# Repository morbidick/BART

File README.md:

# BBQ Thermometer

## Hardware

### Board ([nrf52](https://www.adafruit.com/product/3406))

* [Arduino IDE Setup](https://learn.adafruit.com/bluefruit-nrf52-feather-learning-guide/arduino-bsp-setup)
* [pinout](https://learn.adafruit.com/bluefruit-nrf52-feather-learning-guide/device-pinout)
* [library](https://github.com/adafruit/Adafruit_nRF52_Arduino/)

### Probes

Some NTCs from Senstech (lets use pt1000 next time...) with a stero jack

### Bluetooth

* Environmental Sensing Service: [0x181A](https://www.bluetooth.com/specifications/gatt/viewer?attributeXmlFile=org.bluetooth.service.environmental_sensing.xml)
* Temperature Characteristic: [0x2A1F](https://www.bluetooth.com/specifications/gatt/viewer?attributeXmlFile=org.bluetooth.characteristic.temperature_celsius.xml)
* Payload 5 Bytes: First Byte `0x01` when probe is connected (`0x00` otherwise), int16 Temperature 1, int16 Temperature 2 (Celsius, Exponent -1)

## Frontend

Let's write an awesome PWA with web bluetooth

### Web Bluetooth API

* usage with chrome [activate](chrome://flags/#enable-experimental-web-platform-features) [debug](chrome://bluetooth-internals)
* [inspiration](https://www.youtube.com/watch?v=_4nrh6mTt4E&feature=youtu.be&t=8h19m47s)
* [samples](https://googlechrome.github.io/samples/web-bluetooth/) ([source](https://github.com/GoogleChrome/samples/tree/gh-pages/web-bluetooth))

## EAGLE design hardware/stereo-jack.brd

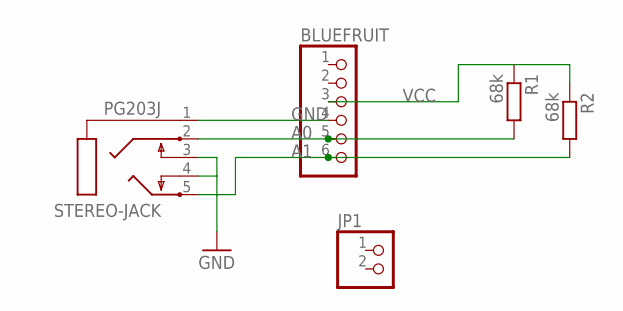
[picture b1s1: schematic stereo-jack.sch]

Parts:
BLUEFRUIT: PINHD-1X6; 1X06
JP1: PINHD-1X2; 1X02
R1, R2: 68k; 0207/7
STEREO-JACK: PG203J

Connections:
A0: BLUEFRUIT.5, R1.2, STEREO-JACK.2
A1: BLUEFRUIT.6, R2.2, STEREO-JACK.5
GND: BLUEFRUIT.4, STEREO-JACK.1, STEREO-JACK.3, STEREO-JACK.4
VCC: BLUEFRUIT.3, R1.1, R2.1

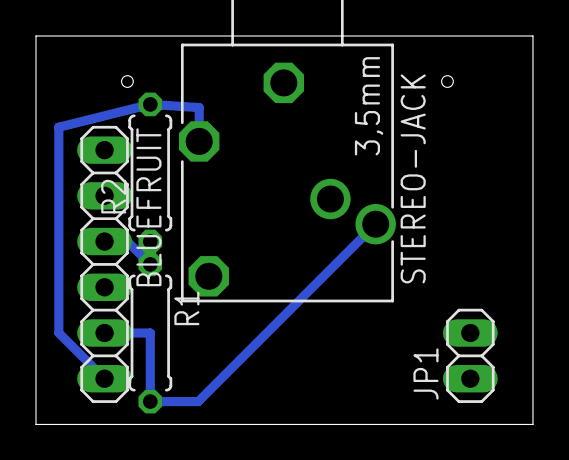
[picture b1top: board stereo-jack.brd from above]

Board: 2 copper layers, 27.6 x 21.6 mm, 5 parts (0 on the bottom side), 4 nets.

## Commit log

2018-07-01 readability
2018-07-01 english pls
2018-07-02 cleanup
2018-07-02 display calculated ntc ressistance for easier debugging
2018-07-08 optimize for serial plotter
2018-07-10 correct measurement
2018-07-10 simplify board schematic and add layout
2018-09-10 lets talk bluetooth
2019-01-07 transmit a string
2019-01-07 transmit the raw value
2019-01-07 cleanup and transmit of the real value in Kelvin*100
2019-01-07 save
2019-01-07 notifications work \o/
2019-01-07 remove vscode file
2019-01-08 only one payload which contains all data
2019-01-09 display missing probe in the frontend
2019-01-10 connect to a specific characteristic
2019-01-14 minimal app
2019-01-14 display errors
2019-01-21 add battery output
2019-01-21 only one service seems to work
2019-01-21 timer all the things
2019-01-29 Add initial FEATURES.md
